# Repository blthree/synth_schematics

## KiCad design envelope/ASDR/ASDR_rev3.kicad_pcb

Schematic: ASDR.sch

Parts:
C1, C2, C5: 10uF; C_Disc_D5.0mm_W2.5mm_P5.00mm
C3: 10nF; C_Disc_D5.0mm_W2.5mm_P5.00mm
C4, C6: 100nF; C_Disc_D5.0mm_W2.5mm_P5.00mm
C7: 1uF; C_Disc_D5.0mm_W2.5mm_P5.00mm
D1, D2: D; D_DO-35_SOD27_P7.62mm_Horizontal
J1: Jack-DC; BarrelJack_CUI_PJ-102AH_Horizontal
J2: Gate In; CUI_SJ2-3592B-SMT-TR
J3: VCA Audio In; CUI_SJ2-3592B-SMT-TR
J4: Glide Control; CUI_SJ2-3592B-SMT-TR
J5: Sample In; CUI_SJ2-3592B-SMT-TR
J6: VCA Out; CUI_SJ2-3592B-SMT-TR
J7: Glide Out; CUI_SJ2-3592B-SMT-TR
J8: Power Out; JST_PH_B3B-PH-K_1x03_P2.00mm_Vertical
J9: ASDR CV Out; CUI_SJ2-3592B-SMT-TR
J10: VCA CV In; CUI_SJ2-3592B-SMT-TR
Q1, Q3, Q4: BC559; TO-92_Inline
Q2: BC548; TO-92_Inline
R1, R10, R20, R21, R22, R25: 33K; R_Axial_DIN0207_L6.3mm_D2.5mm_P5.08mm_Vertical
R2, R4, R11, R14, R16, R18, R29, R30: 1K; R_Axial_DIN0207_L6.3mm_D2.5mm_P5.08mm_Vertical
R3: 22K; R_Axial_DIN0207_L6.3mm_D2.5mm_P5.08mm_Vertical
R5, R12, R13, R15, R17, R23: 10K; R_Axial_DIN0207_L6.3mm_D2.5mm_P5.08mm_Vertical
R6, R7, R8, R9, R26, R27, R28: 1M; R_Axial_DIN0207_L6.3mm_D2.5mm_P5.08mm_Vertical
R19: 100K; R_Axial_DIN0207_L6.3mm_D2.5mm_P5.08mm_Vertical
R24: 5K; R_Axial_DIN0207_L6.3mm_D2.5mm_P5.08mm_Vertical
RV_1, RV_2, RV_3, RV_4: 100K; JST_PH_B3B-PH-K_1x03_P2.00mm_Vertical
RV_A1: 1M; JST_PH_B3B-PH-K_1x03_P2.00mm_Vertical
RV_D1: 1M; JST_PH_B3B-PH-K_1x03_P2.00mm_Vertical
RV_R1: 1M; JST_PH_B3B-PH-K_1x03_P2.00mm_Vertical
RV_S1: 10K; JST_PH_B3B-PH-K_1x03_P2.00mm_Vertical
U1: LTC1044; DIP-8_W7.62mm_Socket
U2, U4: LM324; DIP-14_W7.62mm_Socket
U3: LM13700; DIP-16_W7.62mm_Socket

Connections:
+9V: C4.2, C6.2, J1.1, J8.3, R1.1, R13.1, R17.2, R22.2, R25.1, RV_4.1, U1.8, U2.4 (V+), U3.11 (V+), U4.4 (V+)
-9V: C2.2, J8.1, R27.1, U1.5, U2.11 (V-), U3.6 (V-), U4.11 (V-)
GND: C2.1, C4.1, C5.2, C6.1, C7.1, J1.2, J2.S, J3.S, J4.S, J5.S, J6.S, J7.S, J8.2, J9.S, J10.S, Q1.1 (C), Q2.3 (E), R2.1, R3.2, R8.1, R16.2, R18.2, R23.1, R24.2, RV_1.3, RV_2.3, RV_3.3, U1.3, U4.3 (+)
unnamed: C1.1, U1.2
unnamed: C1.2, U1.4
unnamed: C3.1, R8.2, R9.1, U2.10 (+)
unnamed: C3.2, R6.2, R10.2, U2.1
unnamed: C5.1, RV_A1.2, RV_A1.3, RV_D1.2, RV_D1.3, RV_R1.1, RV_R1.2, U2.12 (+)
unnamed: C7.2, R26.2, U3.5, U4.12 (+)
unnamed: D1.1 (K), RV_A1.1
unnamed: D1.2 (A), R11.1
unnamed: D2.1 (K), RV_S1.2
unnamed: D2.2 (A), RV_D1.1
unnamed: J2.T, R3.1, R4.2
unnamed: J3.T, RV_2.1
unnamed: J4.T, R19.2
unnamed: J5.T, RV_1.1
unnamed: J6.T, R29.1
unnamed: J7.T, R30.1
unnamed: Q1.2 (B), R10.1
unnamed: Q1.3 (E), RV_R1.3
unnamed: Q2.1 (C), RV_4.3
unnamed: Q2.2 (B), RV_1.2
unnamed: Q3.1 (C), U3.1
unnamed: Q3.2 (B), R22.1, RV_4.2
unnamed: Q3.3 (E), R25.2
unnamed: Q4.1 (C), U3.16
unnamed: Q4.2 (B), U4.7
unnamed: Q4.3 (E), R24.1, U4.6 (-)
unnamed: R1.2, R2.2, R5.2, U2.2 (-)
unnamed: R4.1, R6.1, U2.3 (+)
unnamed: R5.1, R7.1, U2.5 (+)
unnamed: R7.2, U2.7
unnamed: R9.2, R11.2, R12.2, U2.8
unnamed: R12.1, RV_S1.3
unnamed: R13.2, RV_S1.1
unnamed: J9.T, J10.T, R14.1, RV_3.1
unnamed: R14.2, U2.6 (-), U2.9 (-), U2.13 (-), U2.14
unnamed: R15.1, R16.1, U3.14 (+)
unnamed: R15.2, RV_2.2
unnamed: R17.1, U3.15 (DIODE_BIAS)
unnamed: R18.1, U3.13 (-)
unnamed: R19.1, U3.3 (+)
unnamed: R20.1, R21.2, U4.2 (-)
unnamed: R20.2, RV_3.2
unnamed: R21.1, U4.1, U4.5 (+)
unnamed: R23.2, U3.12, U4.10 (+)
unnamed: R26.1, R27.2, R28.2
unnamed: R28.1, R30.2, U3.4 (-), U4.13 (-), U4.14
unnamed: R29.2, U4.8, U4.9 (-)
unnamed: U3.7, U3.10

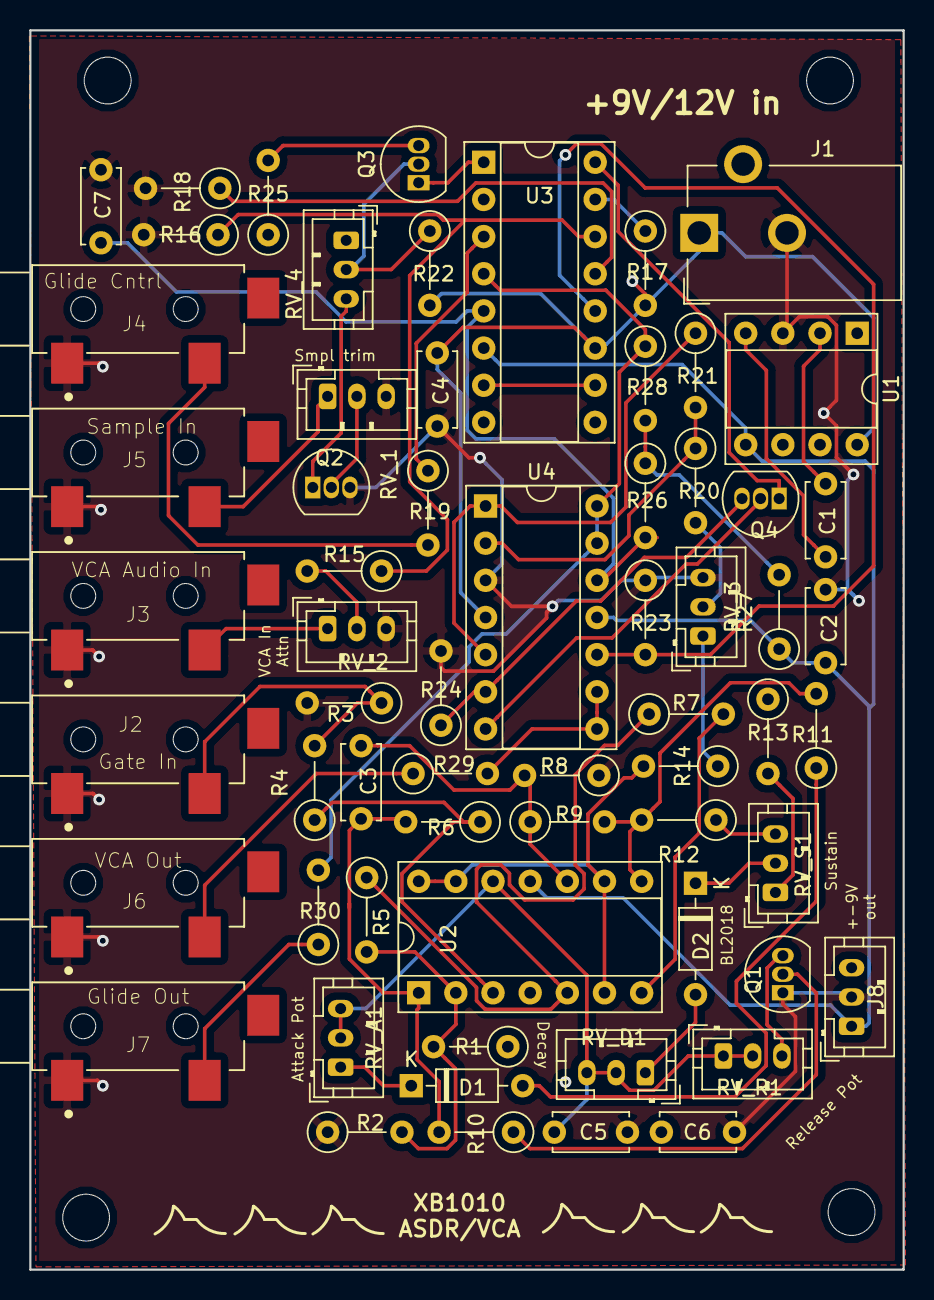
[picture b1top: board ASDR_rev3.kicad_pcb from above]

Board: 2 copper layers, 59.7 x 84.7 mm, 63 parts (0 on the bottom side), 51 nets.

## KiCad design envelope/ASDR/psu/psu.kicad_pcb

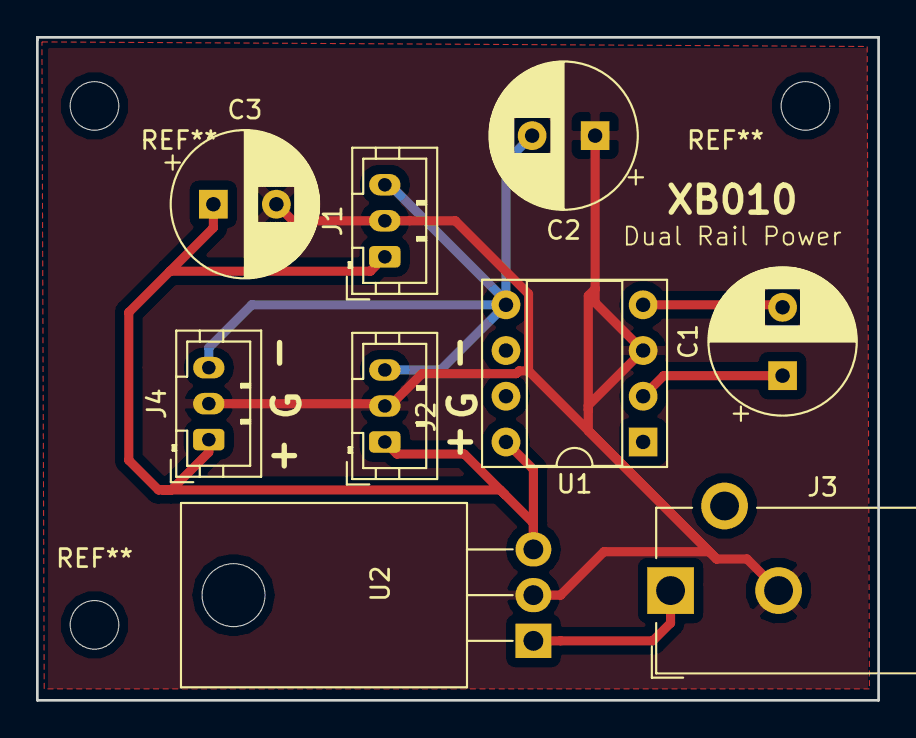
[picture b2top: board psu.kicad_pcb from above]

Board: 2 copper layers, 46.7 x 36.8 mm, 9 parts (0 on the bottom side), 6 nets.

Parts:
C1: 10uF; CP_Radial_D8.0mm_P3.80mm
C2: 100uF; CP_Radial_D8.0mm_P3.50mm
C3: 680uF; CP_Radial_D8.0mm_P3.50mm
J1, J2, J4: +-9V out; JST_PH_B3B-PH-K_1x03_P2.00mm_Vertical
J3: Jack-DC; BarrelJack_CUI_PJ-102AH_Horizontal
U1: LTC1044; DIP-8_W7.62mm_Socket
U2: LF90_TO220; TO-220-3_Horizontal_TabDown

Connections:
+9V: C3.1, J1.1, J2.1, J4.1, U1.8, U2.3
-9V: C2.2, J1.3, J2.3, J4.3, U1.5
GND: C2.1, C3.2, J1.2, J2.2, J3.2, J4.2, U1.3, U2.2
unnamed: C1.1, U1.2
unnamed: C1.2, U1.4
unnamed: J3.1, U2.1

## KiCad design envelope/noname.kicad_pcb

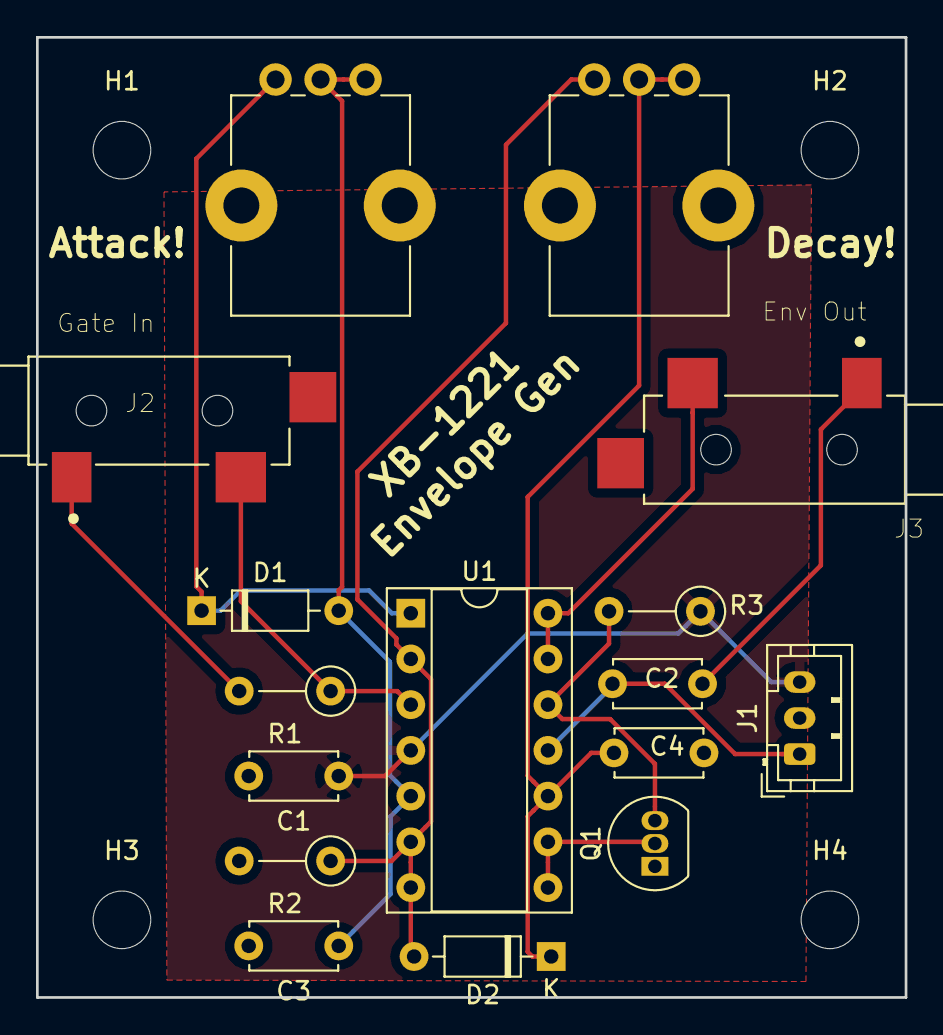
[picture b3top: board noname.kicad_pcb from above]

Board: 2 copper layers, 48.3 x 53.3 mm, 20 parts (0 on the bottom side), 11 nets.

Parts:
C1, C2: 0.1uF; C_Disc_D4.7mm_W2.5mm_P5.00mm
C3, C4: 1uF; C_Disc_D4.7mm_W2.5mm_P5.00mm
D1, D2: D_ALT; D_DO-35_SOD27_P7.62mm_Horizontal
H1, H2, H3, H4: MountingHole; MountingHole_3.2mm_M3_ISO7380
J1: Power; JST_PH_B3B-PH-K_1x03_P2.00mm_Vertical
J2: Gate In; CUI_SJ2-3592B-SMT-TR
J3: Env Out; CUI_SJ2-3592B-SMT-TR
Q1: 2N3906; TO-92_Inline
R1, R2: 1M; R_Axial_DIN0207_L6.3mm_D2.5mm_P5.08mm_Vertical
R3: 100K; R_Axial_DIN0207_L6.3mm_D2.5mm_P5.08mm_Vertical
RV1: 1M Attack; Potentiometer_Bourns_PTV09A-1_Single_Vertical
RV2: 1M Decay; Potentiometer_Bourns_PTV09A-1_Single_Vertical
U1: TL074; DIP-14_W7.62mm_Socket

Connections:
+9V: C1.1, J1.3, R3.1, U1.4
-9V: C2.1, J1.1, U1.11
EG: J3.T, U1.13, U1.14
GND: C1.2, C2.2, C3.2, C4.2, J1.2, J2.S, J3.S, Q1.1, R1.2, R2.2
Gate: J2.T, R1.1, U1.3
unnamed: C3.1, D1.2, RV1.2, RV1.3, U1.5
unnamed: C4.1, D2.1, RV2.2, RV2.3, U1.10
unnamed: D1.1, RV1.1, U1.1
unnamed: D2.2, R2.1, RV2.1, U1.2, U1.6, U1.7
unnamed: Q1.2, U1.8, U1.9
unnamed: Q1.3, R3.2, U1.12

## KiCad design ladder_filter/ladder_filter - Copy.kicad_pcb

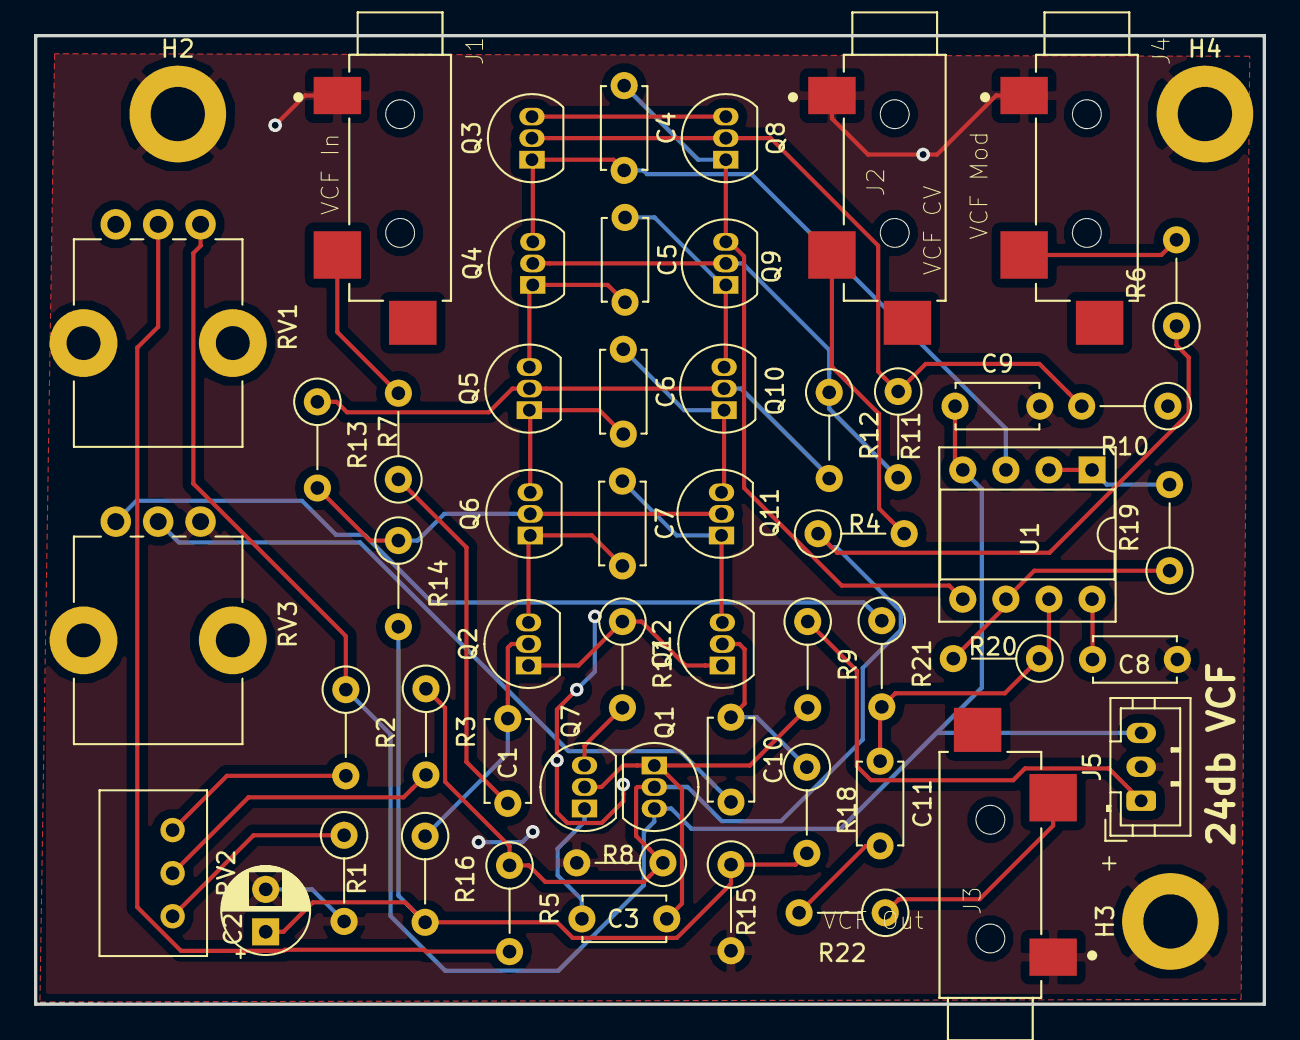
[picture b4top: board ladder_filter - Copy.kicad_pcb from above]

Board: 2 copper layers, 72.4 x 57.1 mm, 57 parts (0 on the bottom side), 38 nets.

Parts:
C1, C10, C11: 2.2uF; C_Disc_D4.7mm_W2.5mm_P5.00mm
C2: 100uF; CP_Radial_D5.0mm_P2.50mm
C3, C4, C5, C6, C7: 0.1uF; C_Disc_D4.7mm_W2.5mm_P5.00mm
C8, C9: 0.10uF; C_Disc_D4.7mm_W2.5mm_P5.00mm
H2, H3, H4: MountingHole_Pad; MountingHole_3.2mm_M3_ISO7380_Pad
J1: VCF In; CUI_SJ2-3592B-SMT-TR
J2: VCF CV; CUI_SJ2-3592B-SMT-TR
J3: VCF Out; CUI_SJ2-3592B-SMT-TR
J4: VCF Mod; CUI_SJ2-3592B-SMT-TR
J5: Power; JST_PH_B3B-PH-K_1x03_P2.00mm_Vertical
Q1: 2N3906; TO-92_Inline
Q2, Q3, Q4, Q5, Q6, Q7, Q8, Q9, Q10, Q11, Q12: 2N3904; TO-92_Inline
R1, R2: 4.99k; R_Axial_DIN0207_L6.3mm_D2.5mm_P5.08mm_Vertical
R3, R7: 68.1k; R_Axial_DIN0207_L6.3mm_D2.5mm_P5.08mm_Vertical
R4: 47.5k; R_Axial_DIN0207_L6.3mm_D2.5mm_P5.08mm_Vertical
R5: 100k; R_Axial_DIN0207_L6.3mm_D2.5mm_P5.08mm_Vertical
R6: 33.2k; R_Axial_DIN0207_L6.3mm_D2.5mm_P5.08mm_Vertical
R8, R11, R12, R13, R14, R16, R17, R18: 1k; R_Axial_DIN0207_L6.3mm_D2.5mm_P5.08mm_Vertical
R9, R21, R22: 12.1k; R_Axial_DIN0207_L6.3mm_D2.5mm_P5.08mm_Vertical
R10, R15: 2.74K; R_Axial_DIN0207_L6.3mm_D2.5mm_P5.08mm_Vertical
R19: 100R; R_Axial_DIN0207_L6.3mm_D2.5mm_P5.08mm_Vertical
R20: 6.81k; R_Axial_DIN0207_L6.3mm_D2.5mm_P5.08mm_Vertical
RV1: 10kb; Potentiometer_Bourns_PTV09A-1_Single_Vertical
RV2: 10k fq Calib.; Potentiometer_Bourns_3299W_Vertical
RV3: 10KA Res; Potentiometer_Bourns_PTV09A-1_Single_Vertical
U1: NE5532; DIP-8_W7.62mm_Socket

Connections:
+9V: C8.2, J5.1, Q3.3, Q8.3, R9.1, R10.1, RV1.1, U1.8
-9V: C9.1, J5.3, Q1.3, R2.1, RV1.3, U1.4
GND: C2.2, C8.1, C9.2, H2.1, H3.1, H4.1, J1.S, J2.S, J3.S, J4.S, J5.2, R1.2, R8.2, R15.2, RV3.3
unnamed: C1.1, R7.1
unnamed: C1.2, Q2.2, R16.1
unnamed: C2.1, R14.2, R15.1, R16.2, R18.2
unnamed: C3.1, Q7.1
unnamed: C3.2, Q1.1, Q7.2, R9.2
unnamed: C4.1, Q8.1, Q9.3, U1.5
unnamed: C4.2, Q3.1, Q4.3, U1.3
unnamed: C5.1, Q9.1, Q10.3
unnamed: C5.2, Q4.1, Q5.3
unnamed: C6.1, Q10.1, Q11.3
unnamed: C6.2, Q5.1, Q6.3
unnamed: C7.1, Q11.1, Q12.3
unnamed: C7.2, Q2.3, Q6.1
unnamed: C10.2, RV3.2
unnamed: C11.1, R20.1, R21.2, U1.7
unnamed: C11.2, R22.2
unnamed: Q1.2, R3.1, R4.1, R5.1, R6.1, R8.1
unnamed: Q3.2, Q8.2, R10.2, R11.1
unnamed: Q4.2, Q9.2, R11.2, R12.1
unnamed: Q7.3, R17.2
unnamed: Q5.2, Q10.2, R12.2, R13.1
unnamed: Q6.2, Q11.2, R13.2, R14.1
unnamed: Q2.1, Q12.1, R17.1
unnamed: R1.1, RV2.1
unnamed: R2.2, RV2.3
unnamed: R3.2, RV2.2
unnamed: R5.2, RV1.2
unnamed: R19.1, R20.2, U1.6
unnamed: R19.2, U1.1, U1.2
unnamed: R21.1, RV3.1
Res_Input: C10.1, Q12.2, R18.1
VCF_EXP_CV: J2.T, R4.2
VCF_In: J1.T, R7.2
VCF_Out: J3.T, R22.1
VCF_mod: J4.T, R6.2

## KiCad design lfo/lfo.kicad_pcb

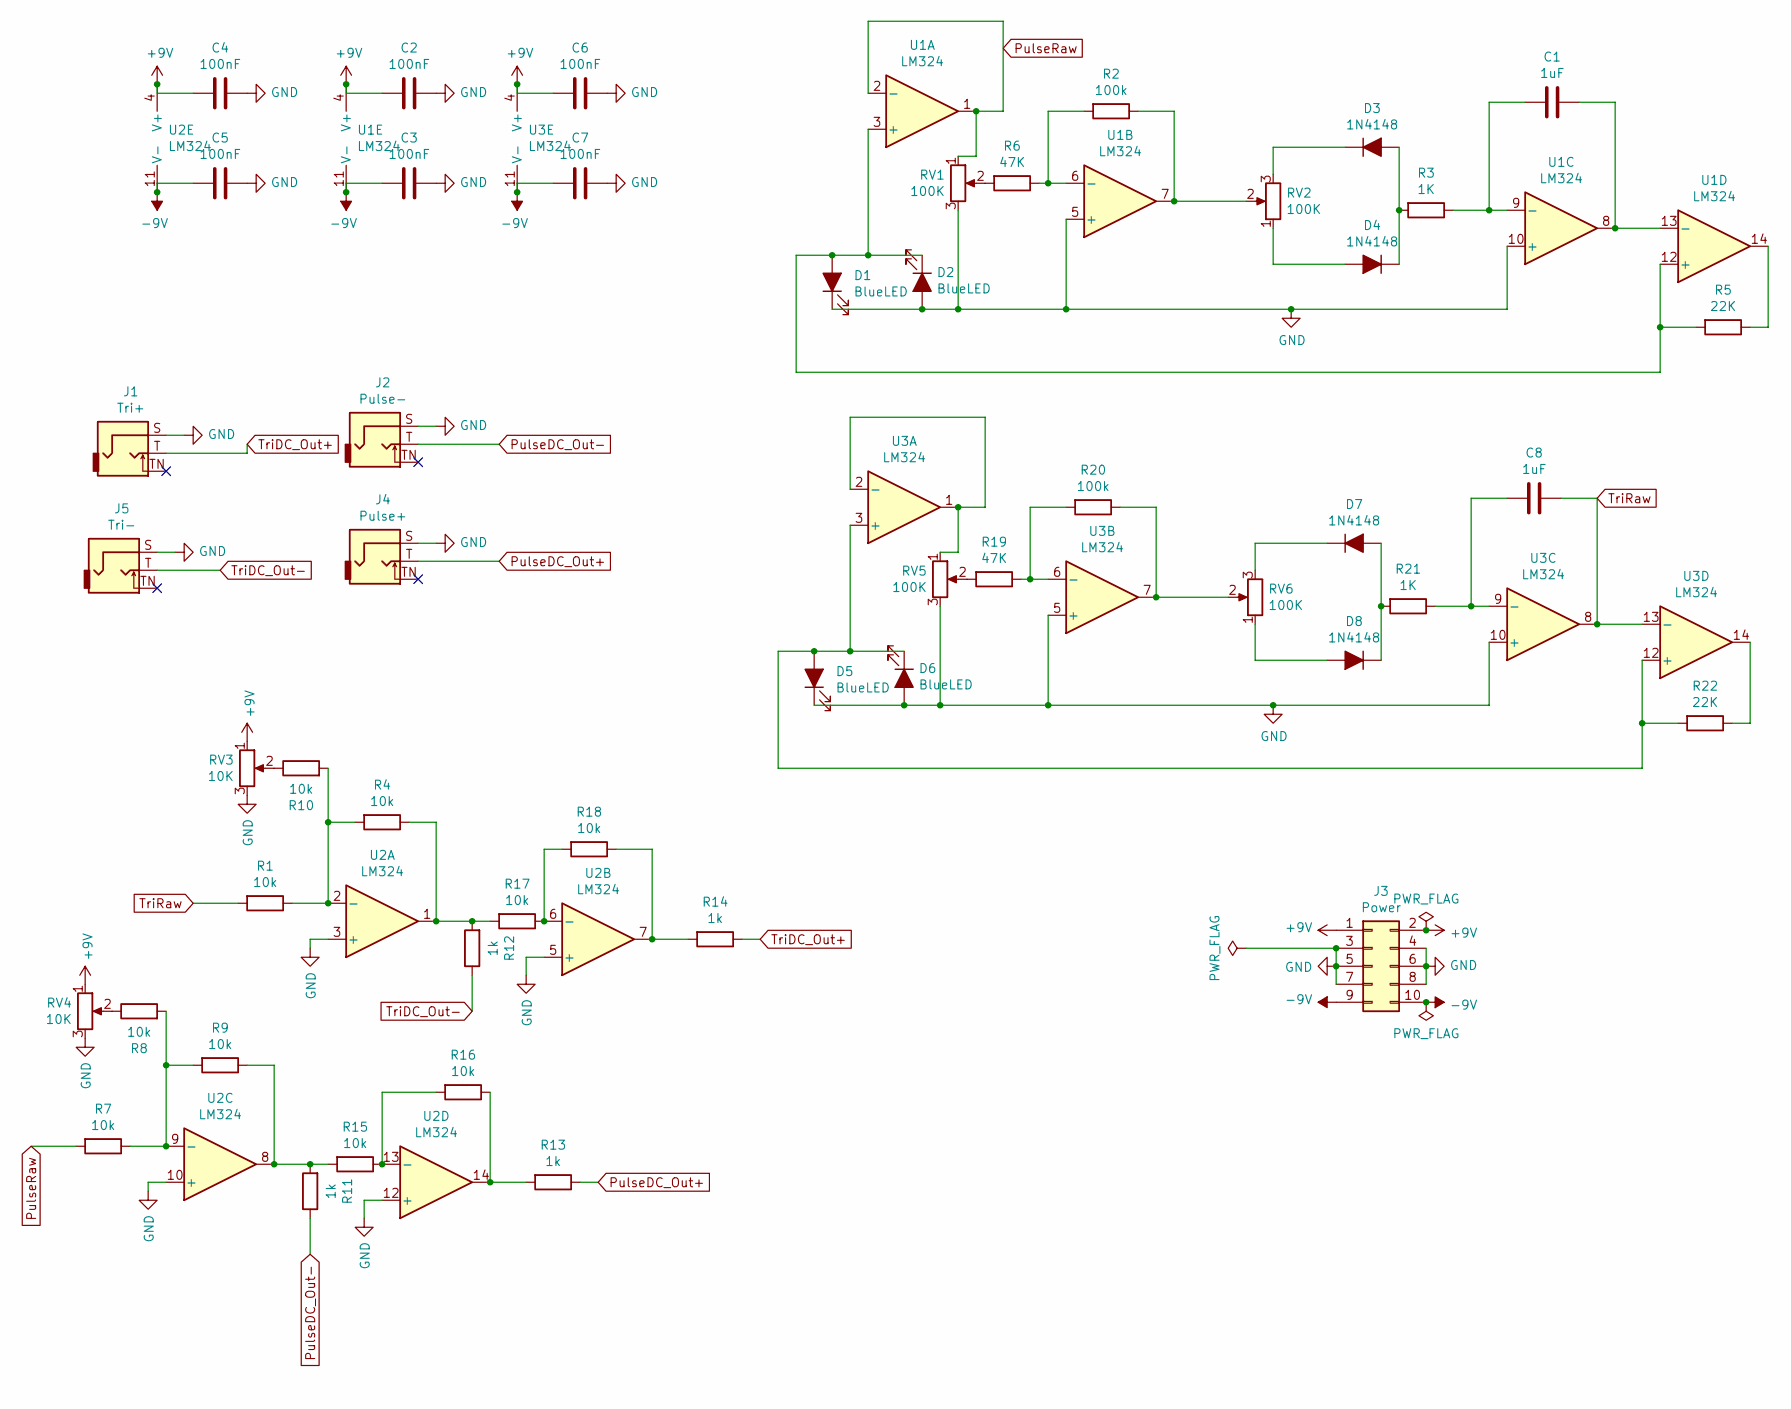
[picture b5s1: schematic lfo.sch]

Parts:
C1, C8: 1uF; C_Disc_D4.7mm_W2.5mm_P5.00mm
C2, C3, C4, C5, C6, C7: 100nF; C_Disc_D4.7mm_W2.5mm_P5.00mm
D1, D2, D5, D6: BlueLED; LED_D5.0mm
D3, D4, D7, D8: 1N4148; D_DO-35_SOD27_P7.62mm_Horizontal
J1: Tri+; Jack_3.5mm_QingPu_WQP-PJ398SM_Vertical_CircularHoles
J2: Pulse-; Jack_3.5mm_QingPu_WQP-PJ398SM_Vertical_CircularHoles
J3: Power; PinHeader_2x05_P2.54mm_Vertical
J4: Pulse+; Jack_3.5mm_QingPu_WQP-PJ398SM_Vertical_CircularHoles
J5: Tri-; Jack_3.5mm_QingPu_WQP-PJ398SM_Vertical_CircularHoles
R1, R4, R7, R8, R9, R10, R15, R16, R17, R18: 10k; R_Axial_DIN0207_L6.3mm_D2.5mm_P5.08mm_Vertical
R2, R20: 100k; R_Axial_DIN0207_L6.3mm_D2.5mm_P5.08mm_Vertical
R3, R21: 1K; R_Axial_DIN0207_L6.3mm_D2.5mm_P5.08mm_Vertical
R5, R22: 22K; R_Axial_DIN0207_L6.3mm_D2.5mm_P5.08mm_Vertical
R6, R19: 47K; R_Axial_DIN0207_L6.3mm_D2.5mm_P5.08mm_Vertical
R11, R12, R13, R14: 1k; R_Axial_DIN0207_L6.3mm_D2.5mm_P5.08mm_Vertical
RV1, RV2, RV5, RV6: 100K; Potentiometer_Bourns_PTV09A-1_Single_Vertical
RV3, RV4: 10K; Potentiometer_Bourns_3296X_Horizontal
U1, U2, U3: LM324; DIP-14_W7.62mm_Socket

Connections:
+9V: C2.2, C4.2, C6.2, J3.1, J3.2, RV3.1, RV4.1, U1.4 (V+), U2.4 (V+), U3.4 (V+)
-9V: C3.2, C5.2, C7.2, J3.9, J3.10, U1.11 (V-), U2.11 (V-), U3.11 (V-)
GND: C2.1, C3.1, C4.1, C5.1, C6.1, C7.1, D1.1 (K), D2.2 (A), D5.1 (K), D6.2 (A), J1.S, J2.S, J3.3, J3.4, J3.5, J3.6, J3.7, J3.8, J4.S, J5.S, RV1.3, RV3.3, RV4.3, RV5.3, U1.5 (+), U1.10 (+), U2.3 (+), U2.5 (+), U2.10 (+), U2.12 (+), U3.5 (+), U3.10 (+)
unnamed: C1.1, U1.8, U1.13 (-)
unnamed: C1.2, R3.1, U1.9 (-)
unnamed: C8.2, R21.1, U3.9 (-)
unnamed: D1.2 (A), D2.1 (K), R5.2, U1.3 (+), U1.12 (+)
unnamed: D3.1 (K), RV2.3
unnamed: D3.2 (A), D4.1 (K), R3.2
unnamed: D4.2 (A), RV2.1
unnamed: D5.2 (A), D6.1 (K), R22.2, U3.3 (+), U3.12 (+)
unnamed: D7.1 (K), RV6.3
unnamed: D7.2 (A), D8.1 (K), R21.2
unnamed: D8.2 (A), RV6.1
unnamed: R1.1, R4.2, R10.2, U2.2 (-)
unnamed: R2.1, RV2.2, U1.7
unnamed: R2.2, R6.1, U1.6 (-)
unnamed: R5.1, U1.14
unnamed: R6.2, RV1.2
unnamed: R7.1, R8.2, R9.2, U2.9 (-)
unnamed: R8.1, RV4.2
unnamed: R10.1, RV3.2
unnamed: R9.1, R11.2, R15.2, U2.8
unnamed: R4.1, R12.2, R17.2, U2.1
unnamed: R13.2, R16.1, U2.14
unnamed: R14.2, R18.1, U2.7
unnamed: R15.1, R16.2, U2.13 (-)
unnamed: R17.1, R18.2, U2.6 (-)
unnamed: R19.1, R20.2, U3.6 (-)
unnamed: R19.2, RV5.2
unnamed: R20.1, RV6.2, U3.7
unnamed: R22.1, U3.14
unnamed: RV5.1, U3.1, U3.2 (-)
PulseDC_Out+: J4.T, R13.1
PulseDC_Out-: J2.T, R11.1
PulseRaw: R7.2, RV1.1, U1.1, U1.2 (-)
TriDC_Out+: J1.T, R14.1
TriDC_Out-: J5.T, R12.1
TriRaw: C8.1, R1.2, U3.8, U3.13 (-)

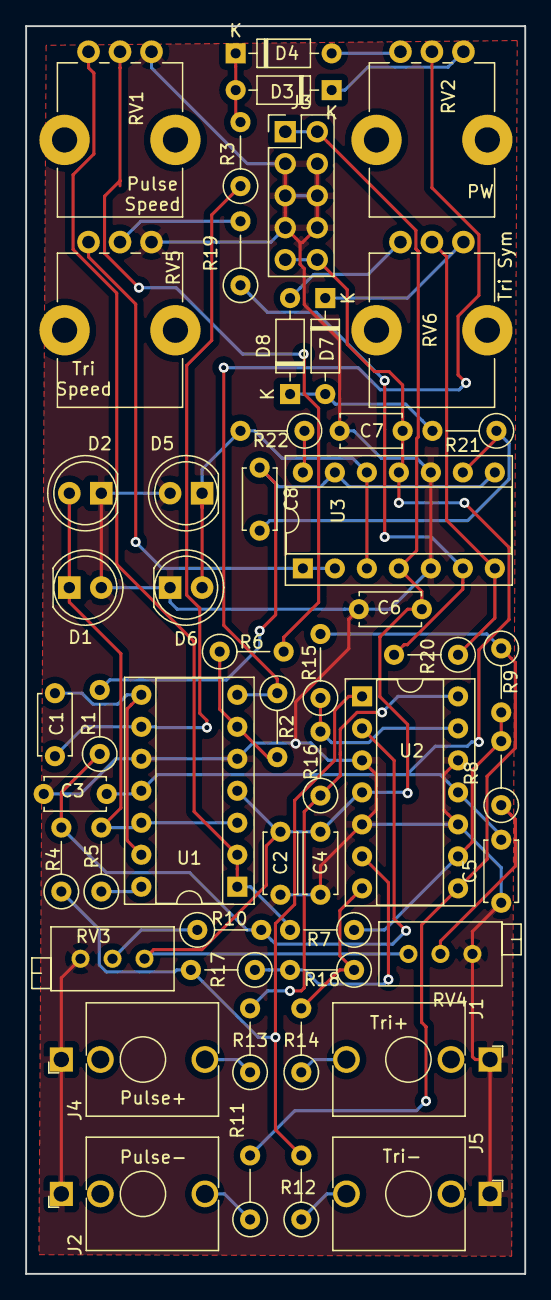
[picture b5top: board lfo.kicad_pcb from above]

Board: 2 copper layers, 39.6 x 99.1 mm, 52 parts (0 on the bottom side), 39 nets.

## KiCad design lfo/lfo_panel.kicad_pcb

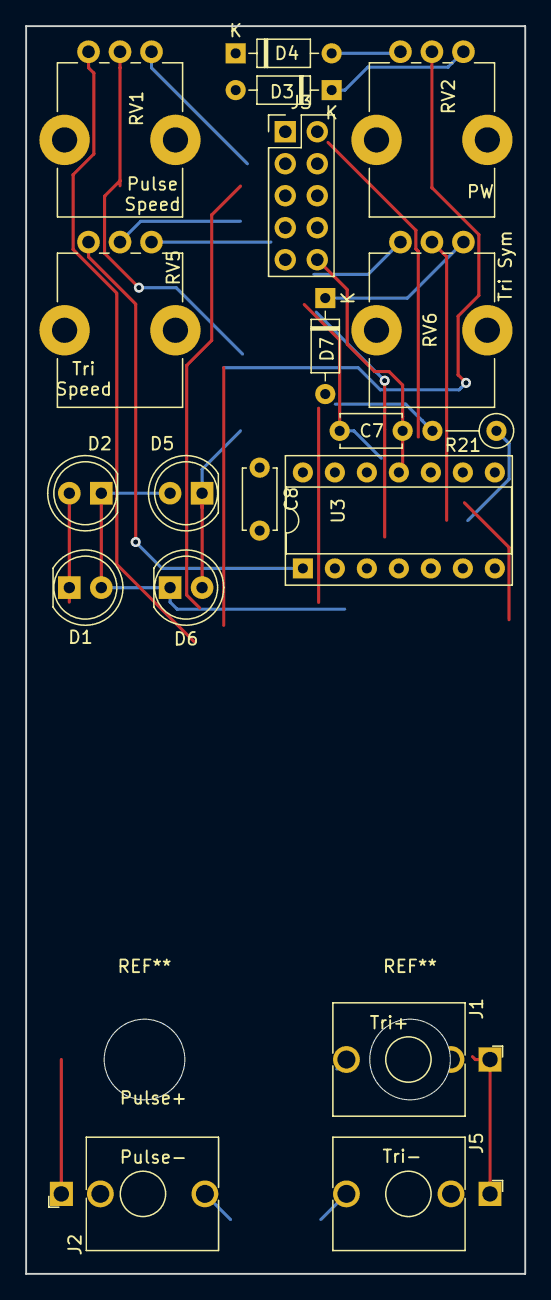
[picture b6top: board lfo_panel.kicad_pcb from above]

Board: 2 copper layers, 39.6 x 99.1 mm, 19 parts (0 on the bottom side), 14 nets.

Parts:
C7: 100nF; C_Disc_D4.7mm_W2.5mm_P5.00mm
C8: 1uF; C_Disc_D4.7mm_W2.5mm_P5.00mm
D1, D2, D5, D6: BlueLED; LED_D5.0mm
D3, D4, D7: 1N4148; D_DO-35_SOD27_P7.62mm_Horizontal
J1: Pulse+; Jack_3.5mm_QingPu_WQP-PJ398SM_Vertical_CircularHoles
J2: Tri+; Jack_3.5mm_QingPu_WQP-PJ398SM_Vertical_CircularHoles
J3: Power; PinHeader_2x05_P2.54mm_Vertical
J5: Pulse-; Jack_3.5mm_QingPu_WQP-PJ398SM_Vertical_CircularHoles
R21: 1K; R_Axial_DIN0207_L6.3mm_D2.5mm_P5.08mm_Vertical
RV1, RV2, RV5, RV6: 100K; Potentiometer_Bourns_PTV09A-1_Single_Vertical
U3: LM324; DIP-14_W7.62mm_Socket

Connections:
+9V: J3.1, J3.2, U3.4
-9V: C7.2, J3.9, J3.10, U3.11
GND: C7.1, D1.1, D2.2, D5.1, D6.2, J1.S, J2.S, J3.3, J3.4, J3.5, J3.6, J3.7, J3.8, J5.S, RV1.3, RV5.3, U3.5, U3.10
unnamed: C8.2, R21.1, U3.9
unnamed: D1.2, D2.1
unnamed: D3.1, RV2.3
unnamed: D3.2, D4.1
unnamed: D4.2, RV2.1
unnamed: D5.2, D6.1, U3.3, U3.12
unnamed: D7.1, RV6.3
unnamed: D7.2, R21.2
unnamed: RV6.2, U3.7
unnamed: RV5.1, U3.1, U3.2
TriRaw: C8.1, U3.8, U3.13

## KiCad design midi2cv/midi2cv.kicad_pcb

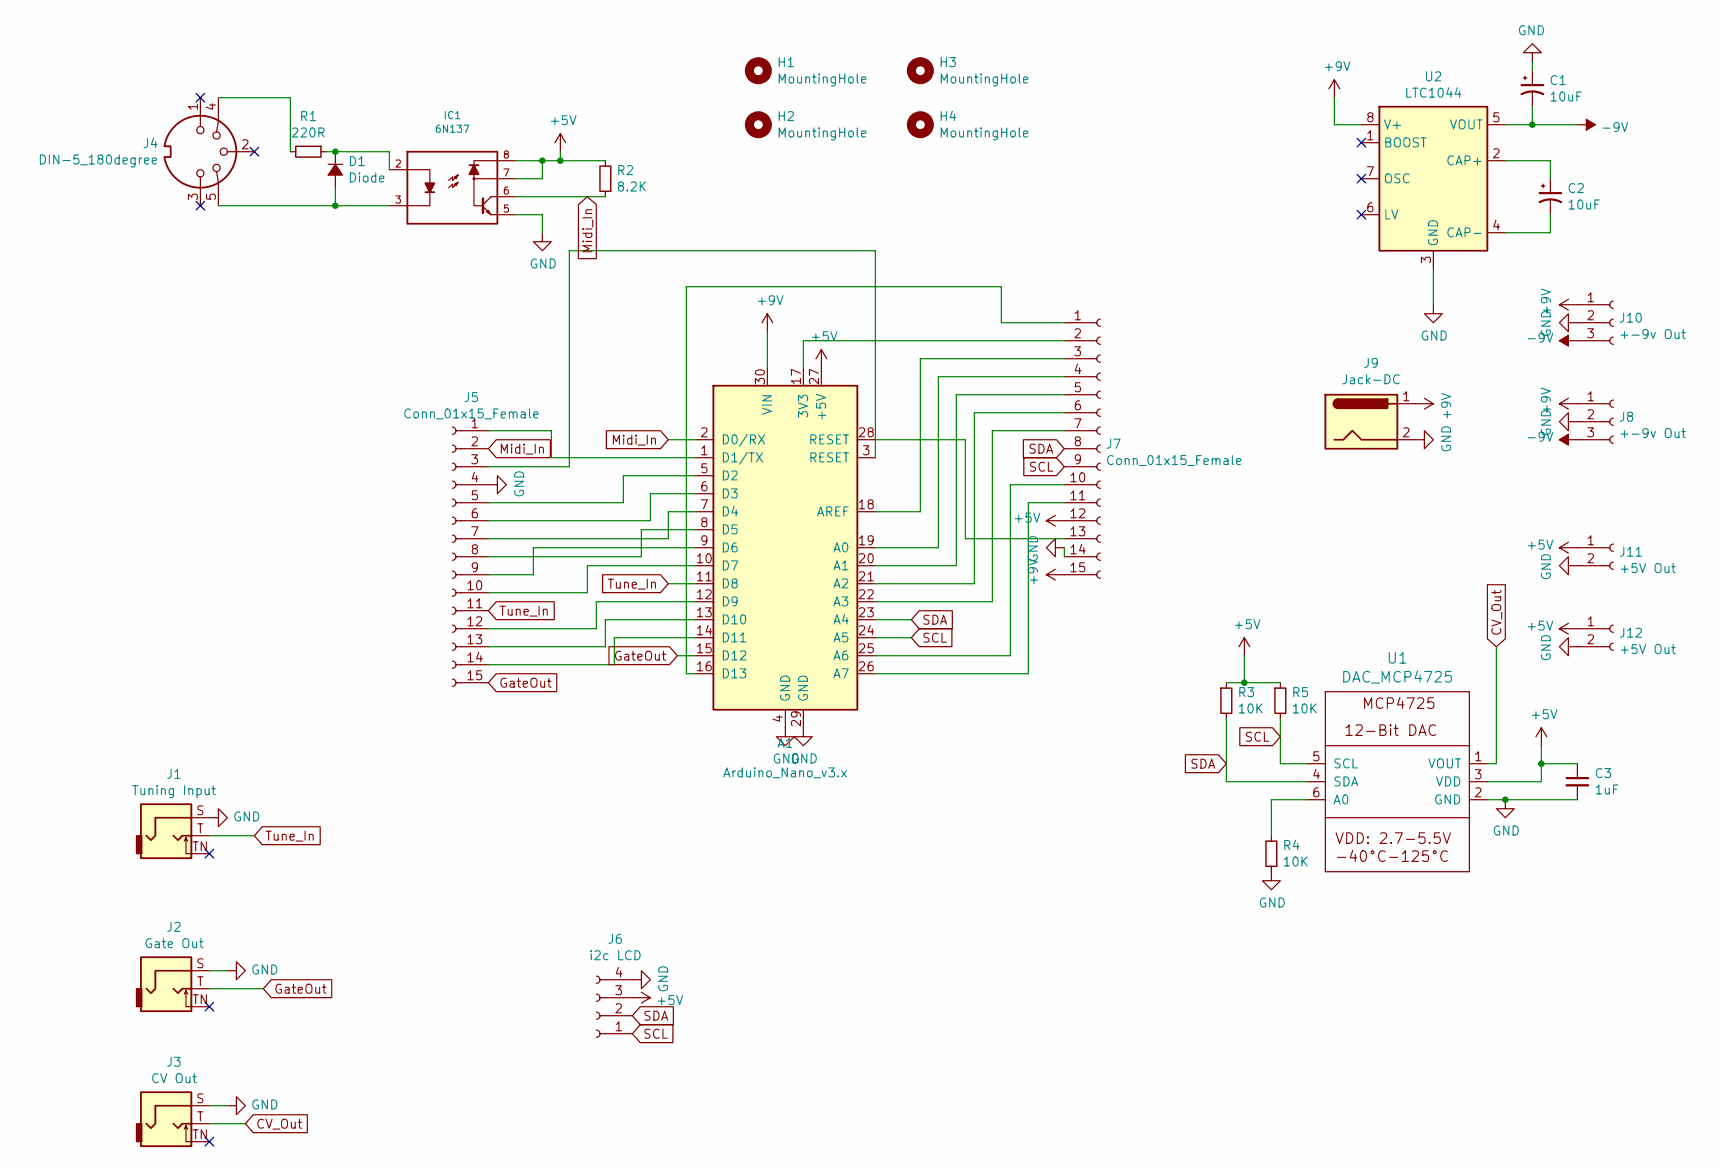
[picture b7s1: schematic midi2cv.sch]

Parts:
A1: Arduino_Nano_v3.x; Arduino_Nano
C1, C2: 10uF; CP_Radial_D5.0mm_P2.50mm
C3: 1uF; C_Disc_D5.0mm_W2.5mm_P5.00mm
D1: Diode; D_DO-35_SOD27_P7.62mm_Horizontal
H1, H2, H3, H4: MountingHole; MountingHole_3.2mm_M3_ISO7380
IC1: 6N137; SMDIP-8_W7.62mm
J1: Tuning Input; CUI_SJ2-3592B-SMT-TR
J2: Gate Out; CUI_SJ2-3592B-SMT-TR
J3: CV Out; CUI_SJ2-3592B-SMT-TR
J4: DIN-5_180degree; SDS-50J
J5, J7: Conn_01x15_Female; PinHeader_1x15_P2.54mm_Vertical
J6: i2c LCD; PinHeader_1x04_P2.54mm_Vertical
J8, J10: +-9v Out; PinHeader_1x03_P2.54mm_Vertical
J9: Jack-DC; BarrelJack_CUI_PJ-102AH_Horizontal
J11, J12: +5V Out; PinHeader_1x02_P2.54mm_Vertical
R1: 220R; R_Axial_DIN0207_L6.3mm_D2.5mm_P5.08mm_Vertical
R2: 8.2K; R_Axial_DIN0207_L6.3mm_D2.5mm_P5.08mm_Vertical
R3, R4, R5: 10K; R_Axial_DIN0207_L6.3mm_D2.5mm_P5.08mm_Vertical
U1: DAC_MCP4725; SOT-23-6_Handsoldering
U2: LTC1044; DIP-8_W7.62mm_Socket

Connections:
+5V: A1.27 (+5V), C3.1, IC1.7, IC1.8, J6.3, J7.12, J11.1, J12.1, R2.2, R3.1, R5.1, U1.3 (VDD)
+9V: A1.30 (VIN), J7.15, J8.1, J9.1, J10.1, U2.8 (V+)
-9V: C1.2, J8.3, J10.3, U2.5 (VOUT)
CV_Out: J3.T, U1.1 (VOUT)
GND: A1.4 (GND), A1.29 (GND), C1.1, C3.2, IC1.5, J1.S, J2.S, J3.S, J5.4, J6.4, J7.14, J8.2, J9.2, J10.2, J11.2, J12.2, R4.1, U1.2 (GND), U2.3 (GND)
GateOut: A1.15 (D12), J2.T, J5.15
Midi_In: A1.2 (D0/RX), IC1.6, J5.2, R2.1
unnamed: A1.1 (D1/TX), J5.1
unnamed: A1.3 (RESET), J5.3
unnamed: A1.5 (D2), J5.5
unnamed: A1.6 (D3), J5.6
unnamed: A1.7 (D4), J5.7
unnamed: A1.8 (D5), J5.8
unnamed: A1.9 (D6), J5.9
unnamed: A1.10 (D7), J5.10
unnamed: A1.12 (D9), J5.12
unnamed: A1.13 (D10), J5.13
unnamed: A1.14 (D11), J5.14
unnamed: A1.16 (D13), J7.1
unnamed: A1.17 (3V3), J7.2
unnamed: A1.18 (AREF), J7.3
unnamed: A1.19 (A0), J7.4
unnamed: A1.20 (A1), J7.5
unnamed: A1.21 (A2), J7.6
unnamed: A1.22 (A3), J7.7
unnamed: A1.25 (A6), J7.10
unnamed: A1.26 (A7), J7.11
unnamed: A1.28 (RESET), J7.13
unnamed: C2.1, U2.2 (CAP+)
unnamed: C2.2, U2.4 (CAP-)
unnamed: D1.1 (K), IC1.2, R1.1
unnamed: D1.2 (A), IC1.3, J4.5
unnamed: J4.4, R1.2
unnamed: R4.2, U1.6 (A0)
SCL: A1.24 (A5), J6.1, J7.9, R5.2, U1.5 (SCL)
SDA: A1.23 (A4), J6.2, J7.8, R3.2, U1.4 (SDA)
Tune_In: A1.11 (D8), J1.T, J5.11

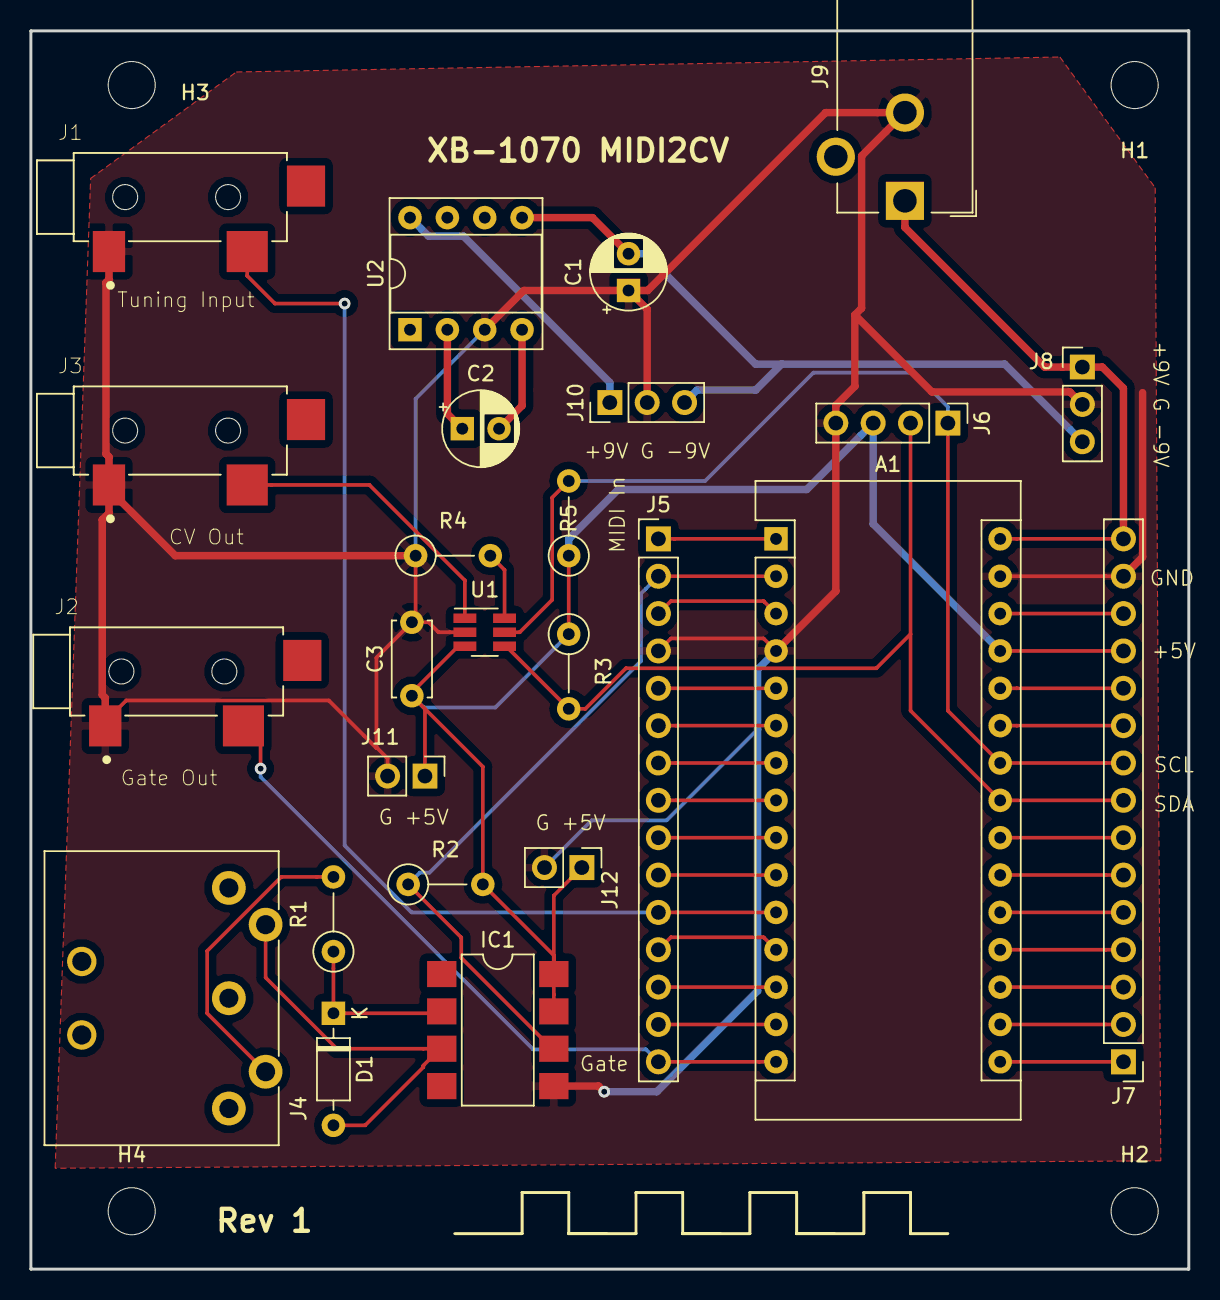
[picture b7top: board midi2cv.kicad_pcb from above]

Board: 2 copper layers, 78.7 x 84.2 mm, 29 parts (0 on the bottom side), 37 nets.
